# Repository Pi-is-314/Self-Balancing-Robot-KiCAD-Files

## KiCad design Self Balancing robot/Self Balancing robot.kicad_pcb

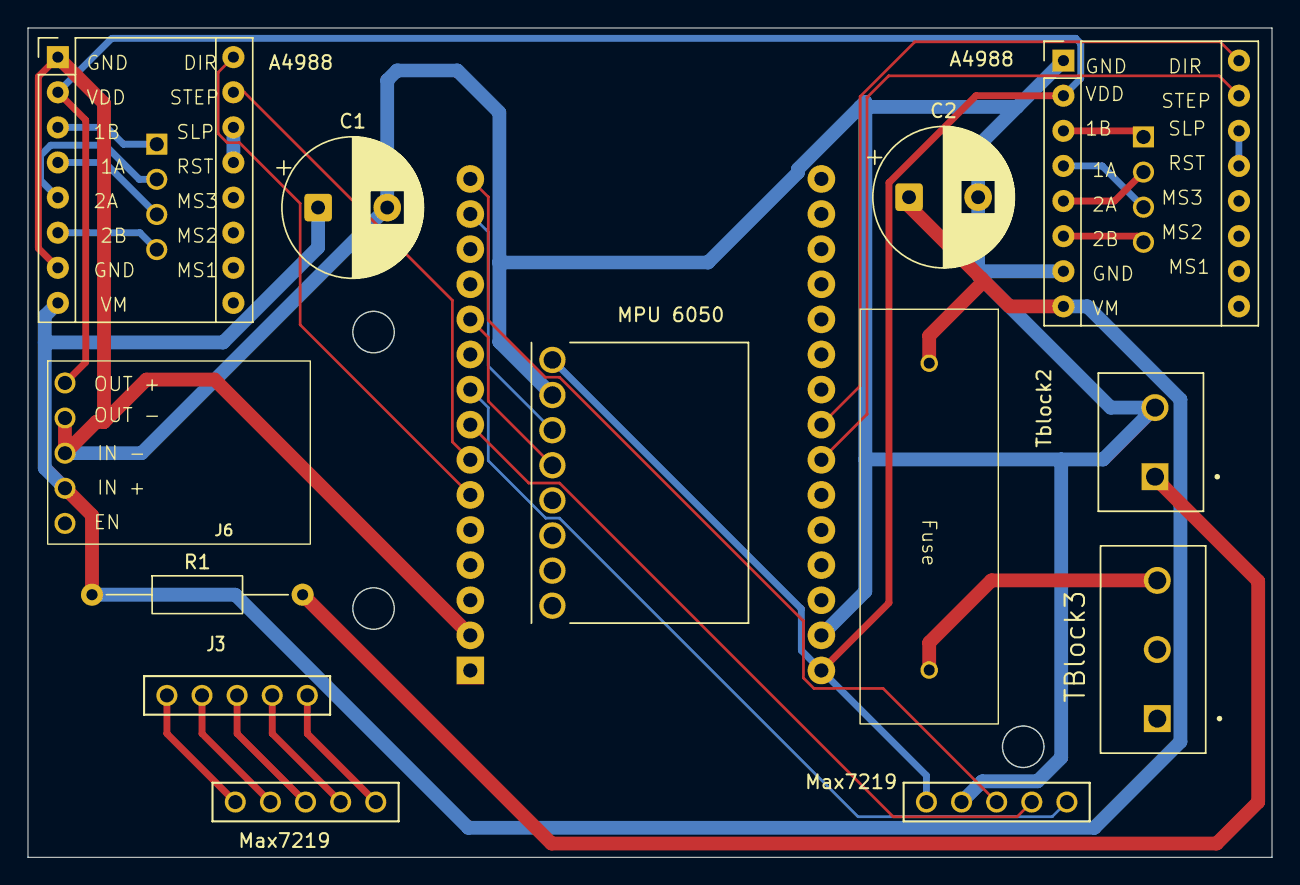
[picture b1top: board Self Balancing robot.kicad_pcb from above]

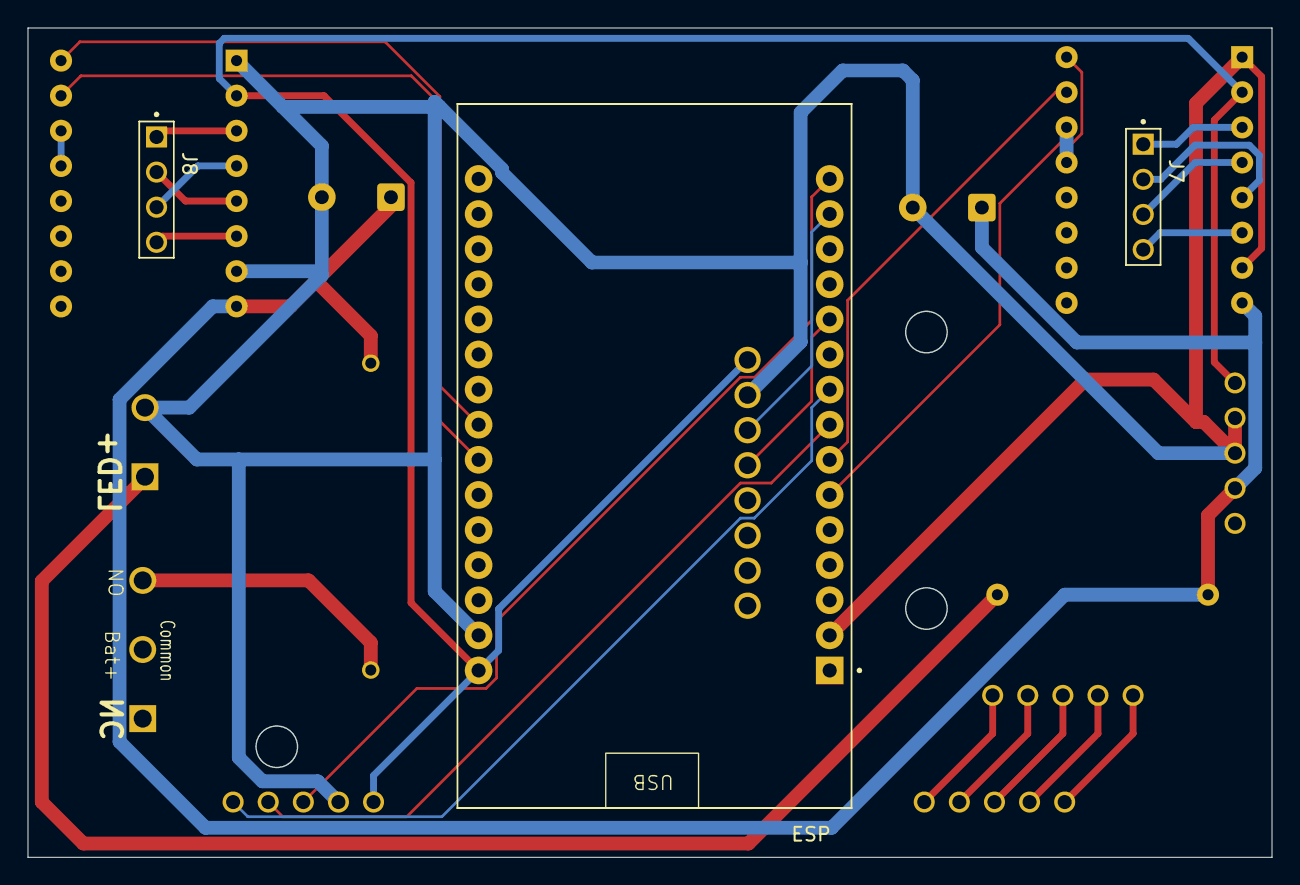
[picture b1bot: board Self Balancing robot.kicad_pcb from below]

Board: 2 copper layers, 90.0 x 60.0 mm, 16 parts (3 on the bottom side), 29 nets.

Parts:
A4988, A4988#2: Pololu_Breakout_A4988; Pololu_Breakout-16_15.2x20.3mm
C1, C2: C; CP_Radial_D10.0mm_P5.00mm
ESP: ESP32-DEVKIT-V1; MODULE_ESP32_DEVKIT_V1
Fuse: 5A Fuse
J3: Max7219 Footprint
J6: 5V buck converter
J7, J8: SSK01-MPH-254-A4; SAMESKY_SSK01-MPH-254-A4
MPU 6050: MPU6050; MODULE_GY-521
Max7219: Max7219 Footprint
Max7219#2: 5 pin male header
R1: R; R_Axial_DIN0207_L6.3mm_D2.5mm_P15.24mm_Horizontal
TBlock3: TB002-500-03BE; CUI_TB002-500-03BE
Tblock2: TB002-500-02BE; CUI_TB002-500-02BE

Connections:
+5V: A4988.2 (VDD), A4988#2.2 (VDD), ESP.30 (VIN), J6.1 (OUT+), MPU 6050.VCC, Max7219.1 (VIN)
+7.5V: A4988.8 (VMOT), A4988#2.8 (VMOT), C1.1, C2.1, Fuse.2 (Output), J6.4 (IN+), R1.1
GND: A4988.1 (GND), A4988.7 (GND), A4988#2.1 (GND), A4988#2.7 (GND), C1.2, C2.2, ESP.2 (GND), ESP.29 (GND), J6.2 (OUT-), J6.3 (IN-), MPU 6050.GND, Max7219.2 (GND), Tblock2.2
unnamed: A4988#2.4 (1A), J7.3
unnamed: A4988#2.3 (1B), J7.1
unnamed: A4988#2.5 (2A), J7.2
unnamed: A4988#2.6 (2B), J7.4
unnamed: A4988#2.16 (DIR), ESP.6 (RX2)
unnamed: A4988#2.15 (STEP), ESP.7 (TX2)
unnamed: A4988#2.13 (~RESET), A4988#2.14 (~SLEEP)
unnamed: A4988.4 (1A), J8.3
unnamed: A4988.3 (1B), J8.1
unnamed: A4988.5 (2A), J8.2
unnamed: A4988.6 (2B), J8.4
unnamed: A4988.16 (DIR), ESP.23 (D25)
unnamed: A4988.15 (STEP), ESP.24 (D26)
unnamed: A4988.13 (~RESET), A4988.14 (~SLEEP)
unnamed: R1.2, Tblock2.1
unnamed: ESP.9 (D18), Max7219.5 (CLK)
unnamed: ESP.8 (D5), Max7219.4 (CS)
unnamed: ESP.15 (D23), Max7219.3 (DIN)
unnamed: J3.5 (CLK), Max7219#2.5
unnamed: J3.4 (CS), Max7219#2.4
unnamed: J3.3 (DIN), Max7219#2.3
unnamed: J3.2 (GND), Max7219#2.2
unnamed: J3.1 (VIN), Max7219#2.1
unnamed: ESP.11 (D21), MPU 6050.SDA
unnamed: ESP.14 (D22), MPU 6050.SCL
unnamed: Fuse.1 (Input), TBlock3.3 (3_3)
